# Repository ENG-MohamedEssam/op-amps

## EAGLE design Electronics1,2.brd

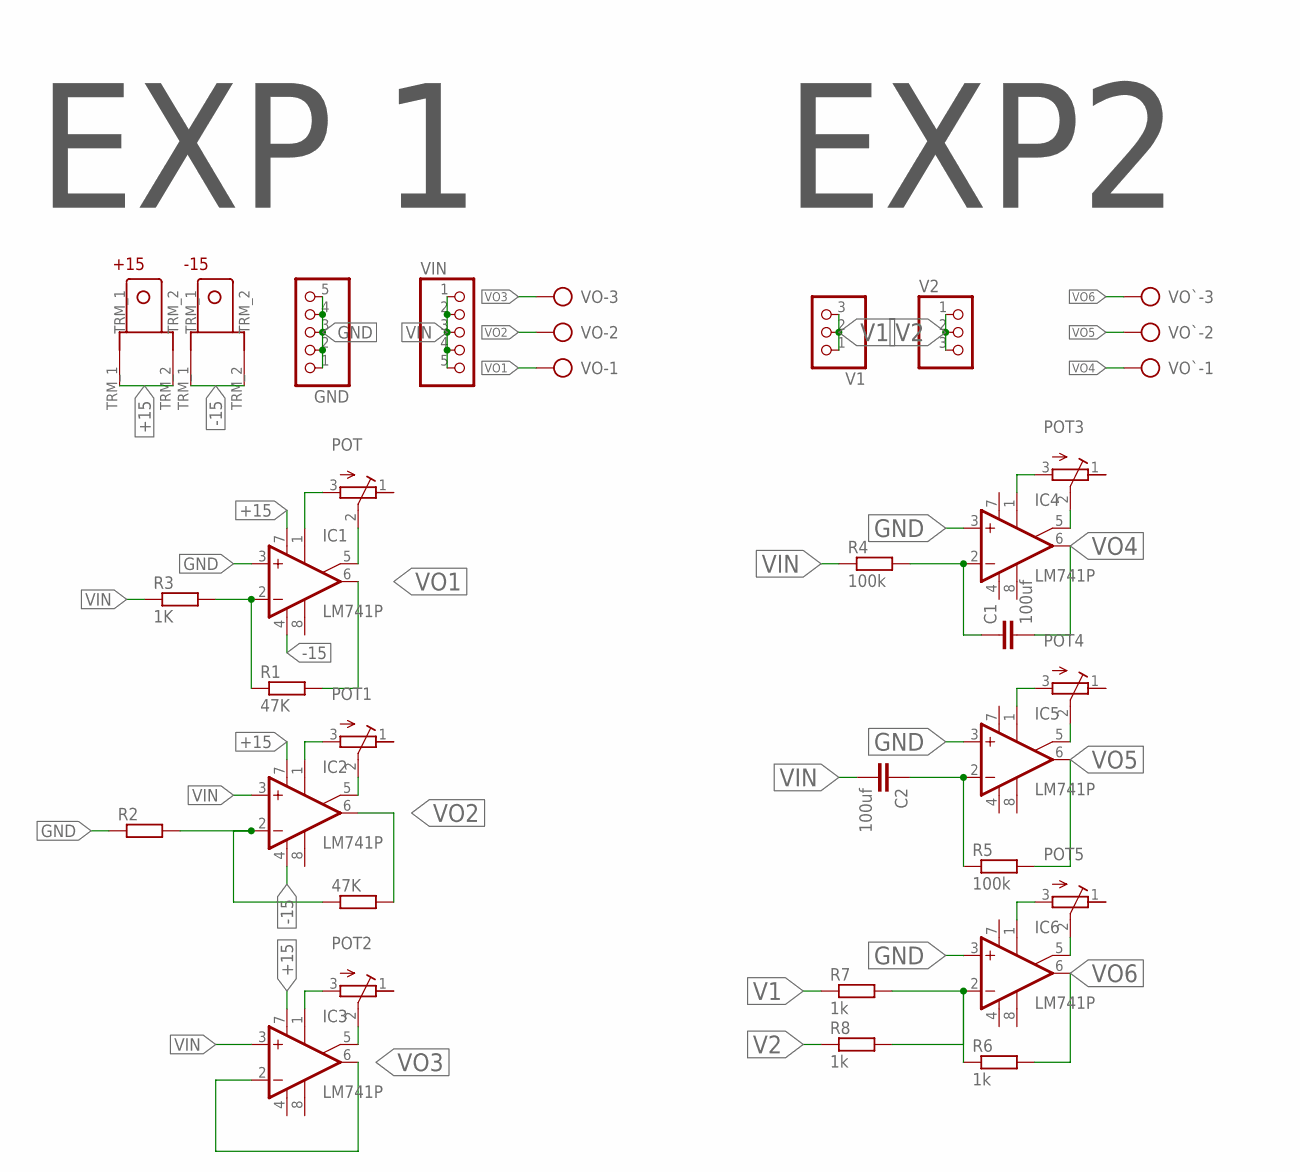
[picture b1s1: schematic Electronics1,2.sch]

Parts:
47K: R-EU_0204/7; 0204/7
+15: TERMINAL_EDITED
-15: TERMINAL_EDITED
C1, C2: 100uf; C025-025X050
GND: PINHD-1X5; 1X05
IC1, IC2, IC3, IC4, IC5, IC6: LM741P; DIL08
POT, POT1, POT2, POT3, POT4, POT5: R-TRIMMT93XA; RTRIMT93XA
R1: 47K; 0204/7
R2: R-EU_0204/7; 0204/7
R3: 1K; 0204/7
R4, R5: 100k; 0204/7
R6, R7, R8: 1k; 0204/7
V1, V2: PINHD-1X3; 1X03
VIN: PINHD-1X5; 1X05
VO: CON_PTR_3; AK300/3
VO`: CON_PTR_3; AK300/3

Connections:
+15: +15.TRM_1, +15.TRM_2, IC1.7 (V+), IC2.7 (V+), IC3.7 (V+)
-15: -15.TRM_1, -15.TRM_2, IC1.4 (V-), IC2.4 (V-)
GND: GND.1, GND.2, GND.3, GND.4, GND.5, IC1.3 (+IN), IC4.3 (+IN), IC5.3 (+IN), IC6.3 (+IN), R2.1
unnamed: IC1.5 (ON2), POT.2 (S)
unnamed: IC1.1 (ON1), POT.3 (A)
unnamed: IC4.5 (ON2), POT3.2 (S)
unnamed: IC1.2 (-IN), R1.1, R3.2
unnamed: IC3.5 (ON2), POT2.2 (S)
unnamed: C1.1, IC4.2 (-IN), R4.2
unnamed: IC3.1 (ON1), POT2.3 (A)
unnamed: IC2.5 (ON2), POT1.2 (S)
unnamed: IC2.1 (ON1), POT1.3 (A)
unnamed: IC4.1 (ON1), POT3.3 (A)
unnamed: 47K.1, IC2.2 (-IN), R2.2
unnamed: IC5.5 (ON2), POT4.2 (S)
unnamed: C2.1, IC5.2 (-IN), R5.1
unnamed: IC5.1 (ON1), POT4.3 (A)
unnamed: IC6.5 (ON2), POT5.2 (S)
unnamed: IC6.1 (ON1), POT5.3 (A)
unnamed: IC6.2 (-IN), R6.1, R7.2, R8.2
V1: R7.1, V1.1, V1.2, V1.3
V2: R8.1, V2.1, V2.2, V2.3
V+: IC4.7 (V+), IC5.7 (V+), IC6.7 (V+)
V-: IC3.4 (V-), IC4.4 (V-), IC5.4 (V-), IC6.4 (V-)
VIN: C2.2, IC2.3 (+IN), IC3.3 (+IN), R3.1, R4.1, VIN.1, VIN.2, VIN.3, VIN.4, VIN.5
VO1: IC1.6 (OUT), R1.2, VO.1
VO2: 47K.2, IC2.6 (OUT), VO.2
VO3: IC3.2 (-IN), IC3.6 (OUT), VO.3
VO4: C1.2, IC4.6 (OUT), VO`.1
VO5: IC5.6 (OUT), R5.2, VO`.2
VO6: IC6.6 (OUT), R6.2, VO`.3

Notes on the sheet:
EXP 1
EXP2

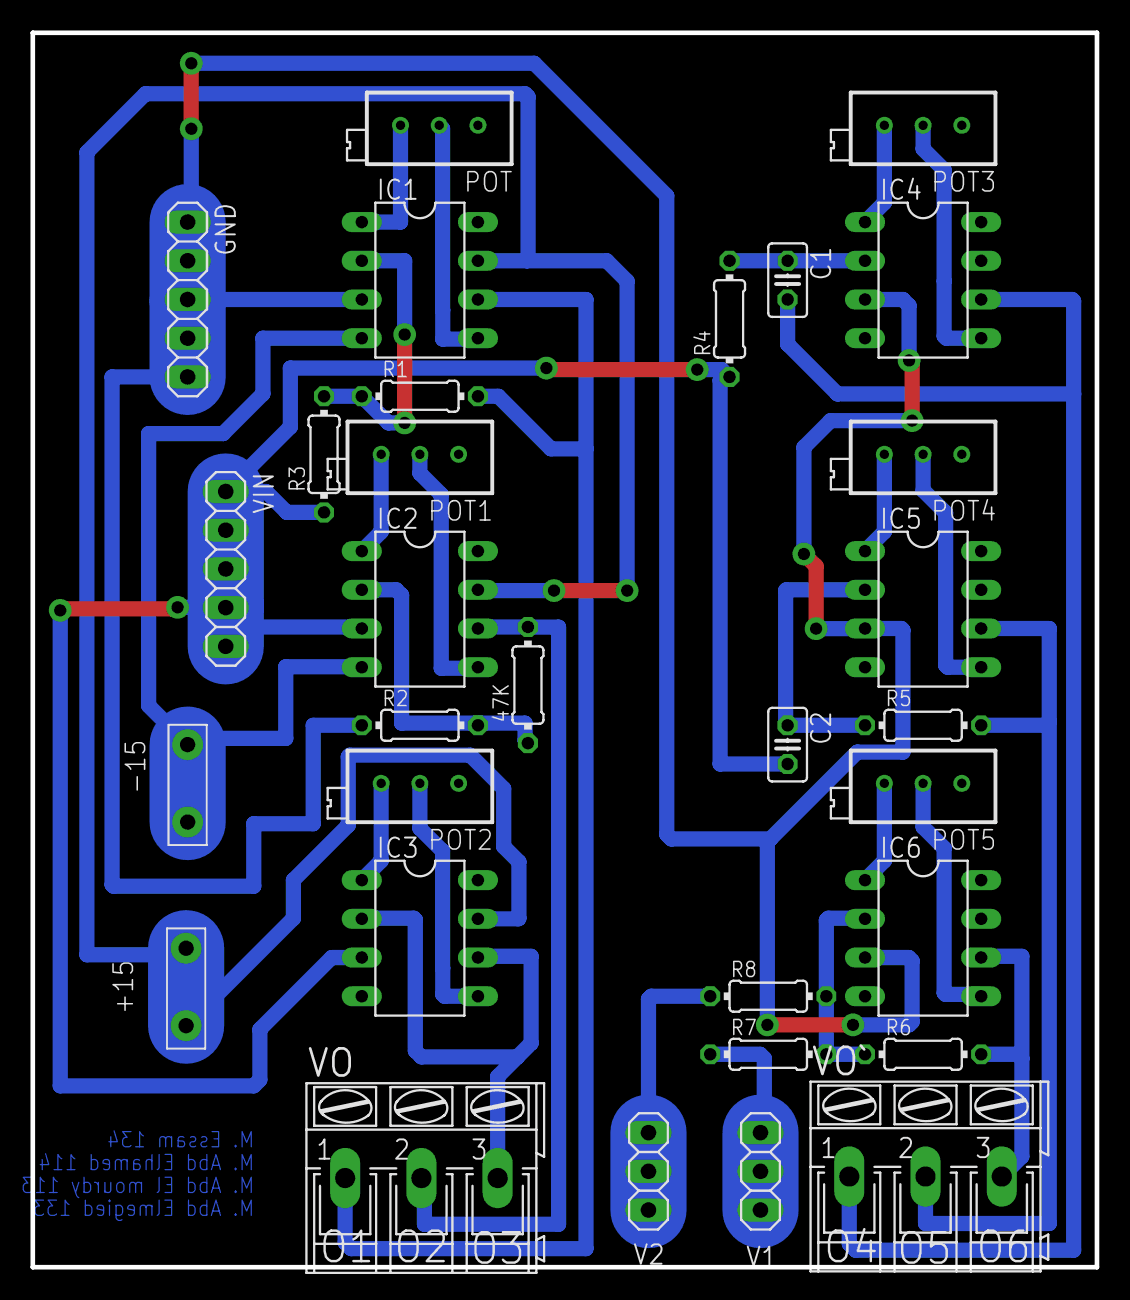
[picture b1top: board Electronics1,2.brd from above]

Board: 2 copper layers, 69.8 x 81.0 mm, 31 parts (0 on the bottom side), 31 nets.
